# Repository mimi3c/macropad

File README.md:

# Macropad
This macropad has 5 keys, 2 LEDs and a 128x32 OLED Display. It is stored in a 3D printed case held with M3x16mm screws.

## PCB:

## Schematic:

## Case:

## BOM of Parts:
- 1x XIAO RP2040
- 0.91" 128x32 OLED Display
- 5x Cherry MX Switches
- 5x DSA Keycaps
- 2x SK6812 MINI-E LEDs

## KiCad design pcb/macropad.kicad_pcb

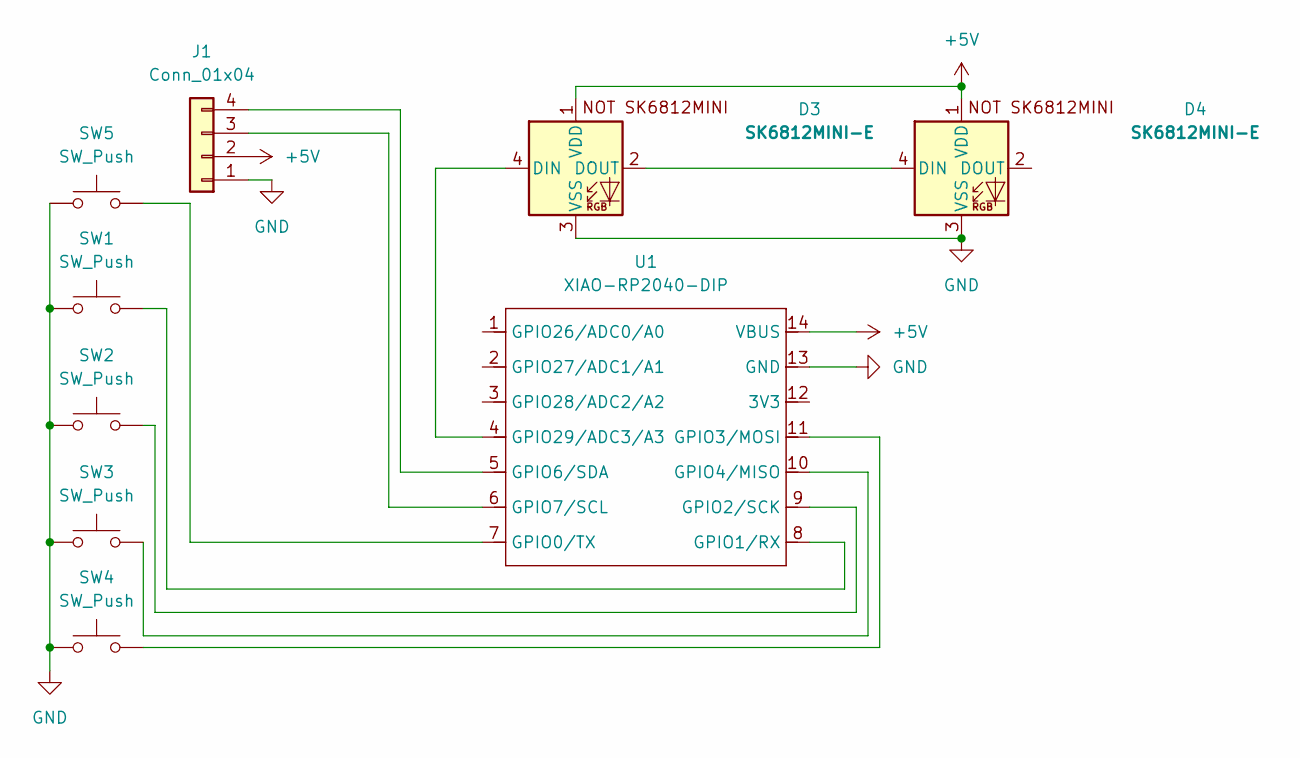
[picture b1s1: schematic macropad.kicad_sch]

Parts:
D3, D4: SK6812MINI-E; SK6812MINI-E_fixed
J1: Conn_01x04; SSD1306-0.91-OLED-4pin-128x32
SW1, SW2, SW3, SW4, SW5: SW_Push; SW_Cherry_MX_1.00u_PCB
U1: XIAO-RP2040-DIP

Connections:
+5V: D3.1 (VDD), D4.1 (VDD), J1.2, U1.14 (VBUS)
GND: D3.3 (VSS), D4.3 (VSS), J1.1, SW1.1, SW2.1, SW3.1, SW4.1, SW5.1, U1.13 (GND)
unnamed: D3.4 (DIN), U1.4 (GPIO29/ADC3/A3)
unnamed: D3.2 (DOUT), D4.4 (DIN)
unnamed: J1.3, U1.6 (GPIO7/SCL)
unnamed: J1.4, U1.5 (GPIO6/SDA)
unnamed: SW5.2, U1.7 (GPIO0/TX)
unnamed: SW1.2, U1.8 (GPIO1/RX)
unnamed: SW2.2, U1.9 (GPIO2/SCK)
unnamed: SW4.2, U1.11 (GPIO3/MOSI)
unnamed: SW3.2, U1.10 (GPIO4/MISO)

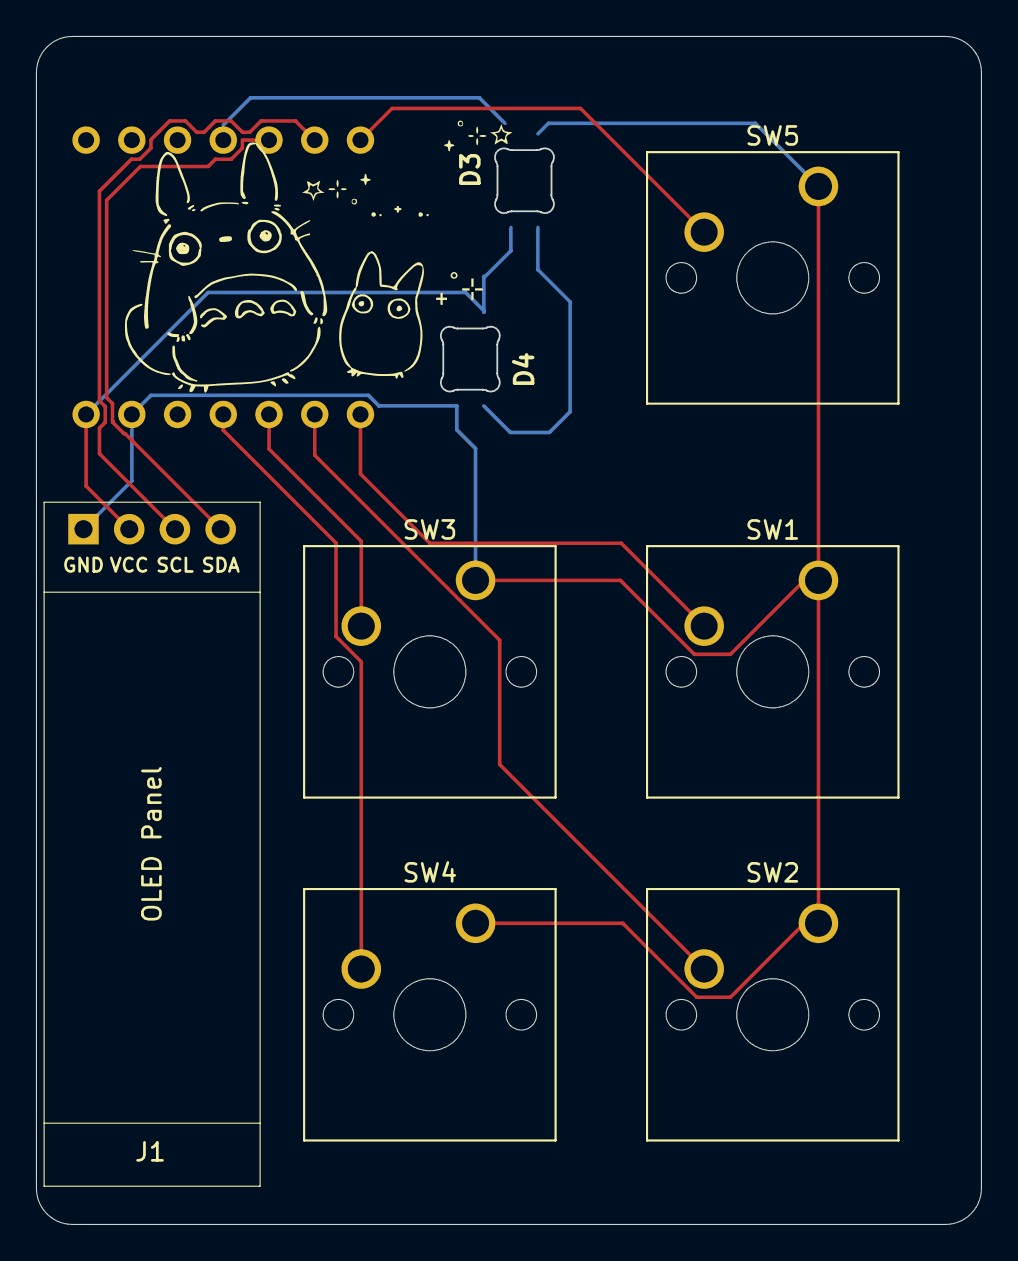
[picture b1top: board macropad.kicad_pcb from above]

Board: 2 copper layers, 52.5 x 66.0 mm, 9 parts (1 on the bottom side), 11 nets.

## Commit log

2026-02-02 update README and project files
2026-02-02 update firmware
